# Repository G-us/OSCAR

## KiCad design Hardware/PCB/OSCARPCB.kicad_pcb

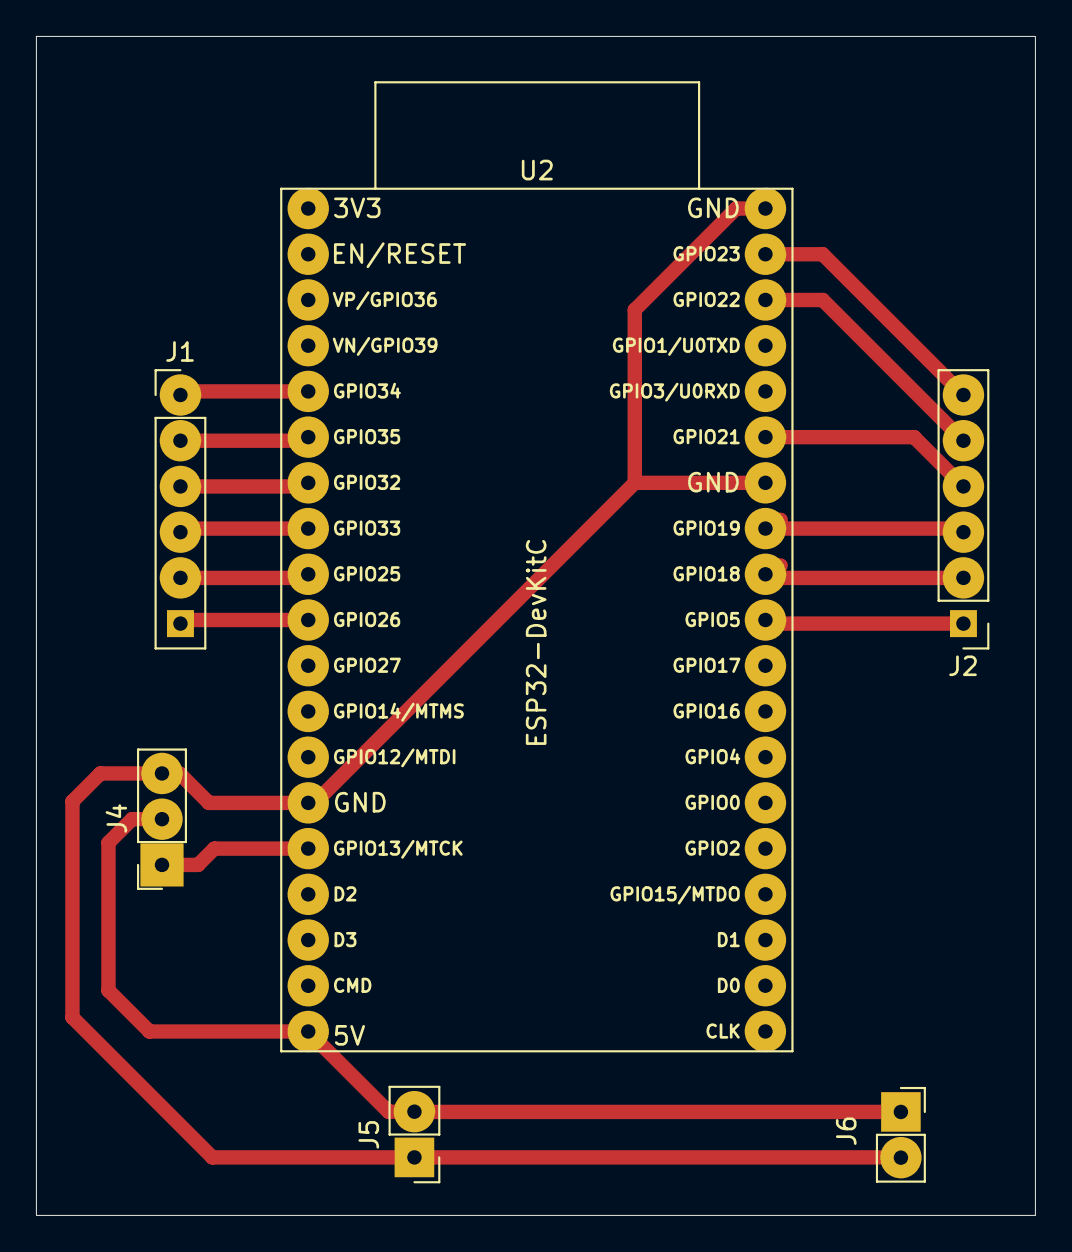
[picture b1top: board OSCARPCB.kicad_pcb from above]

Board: 2 copper layers, 55.5 x 65.5 mm, 6 parts (0 on the bottom side), 15 nets.

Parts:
J1: DC Motor; PinHeader_1x06_P2.54mm_Vertical
J2: Stepper Motor; PinHeader_1x06_P2.54mm_Vertical
J4: Servo OUT; PinSocket_1x03_P2.54mm_Vertical
J5: Power Input; PinHeader_1x02_P2.54mm_Vertical
J6: PINHD_1x2_Female; PinSocket_1x02_P2.54mm_Vertical
U2: ESP32-DevKitC

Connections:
GND: J4.3, J5.1, J6.2, U2.14 (GND), U2.32 (GND), U2.38 (GND)
L Motor 1: J1.2, U2.6 (VDET_2/GPIO35/ADC1_CH7)
L Motor 2: J1.3, U2.7 (32K_XP/GPIO32/ADC1_CH4)
L Motor EN: J1.1, U2.5 (VDET_1/GPIO34/ADC1_CH6)
unnamed: J2.1, U2.29 (GPIO5)
unnamed: J2.2, U2.30 (GPIO18)
unnamed: J2.3, U2.31 (GPIO19)
unnamed: J2.4, U2.33 (GPIO21)
unnamed: J2.5, U2.36 (GPIO22)
unnamed: J2.6, U2.37 (GPIO23)
unnamed: J4.1, U2.15 (MTCK/GPIO13/ADC2_CH4)
R EN: J1.6, U2.10 (DAC_2/ADC2_CH9/GPIO26)
R Motor 3: J1.4, U2.8 (32K_XN/GPIO33/ADC1_CH5)
R Motor 4: J1.5, U2.9 (DAC_1/ADC2_CH8/GPIO25)
VBATT: J4.2, J5.2, J6.1, U2.19 (5V)

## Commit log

2025-09-14 Initial Commit V3
2025-09-14 Update .gitignore and change video capture device index
2025-09-14 added new dataset
2025-09-15 Change video capture device index and refine object detection logic for 'person'
2025-10-22 Add initial OSCARPCB KiCad project files and models
    Added new KiCad PCB, schematic, project, and related configuration files for the OSCARPCB hardware. Included backup ZIP, footprint info cache, and initial YOLO model and args.yaml files for the softw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
2025-11-05 Added ESP32 Cam
2025-11-12 Started PCB schematic
2025-11-12 Started routing PCB
2025-11-14 changed sch to fit PCB better
2025-11-14 PCB V1
2025-11-19 Added OSCARCAM and it works!
2025-11-28 Starting to work with camera streaming
2025-12-03 Started progress on streaming video to python server
2025-12-10 Add initial project structure and files for OSCARMOTORTEST
2026-01-08 Streaming works?
2026-01-08 Updated PCB becasue Im using external components
2026-01-08 No lock
2026-01-16 Control Motors stRT
2026-01-21 Stepper Motor testing
2026-01-22 Stepper Motor Wokrs
2026-01-28 Add workspace configuration and initial sendCommand script
2026-01-30 Starting the reorganization for the laptop-bridge-esp implementation
2026-02-03 PCB Done?
2026-02-03 Make it so that the robot goes forward when joystick forward
2026-02-04 update for debugging
2026-02-04 Maybe fix motor timeout
2026-02-09 Increased resillicance towards errors
2026-02-11 REplaced third motor with stepper motor
2026-02-18 Updated max stepper motor speed.
2026-02-18 Added ability to cancel emergency stop without reseting
2026-03-04 Exported STEP file
2026-03-10 ESP32 Can now control stepper motor (wrong pin assignment) Can now set absolute or relative positions from python!!
2026-03-19 FINAL VERSION
